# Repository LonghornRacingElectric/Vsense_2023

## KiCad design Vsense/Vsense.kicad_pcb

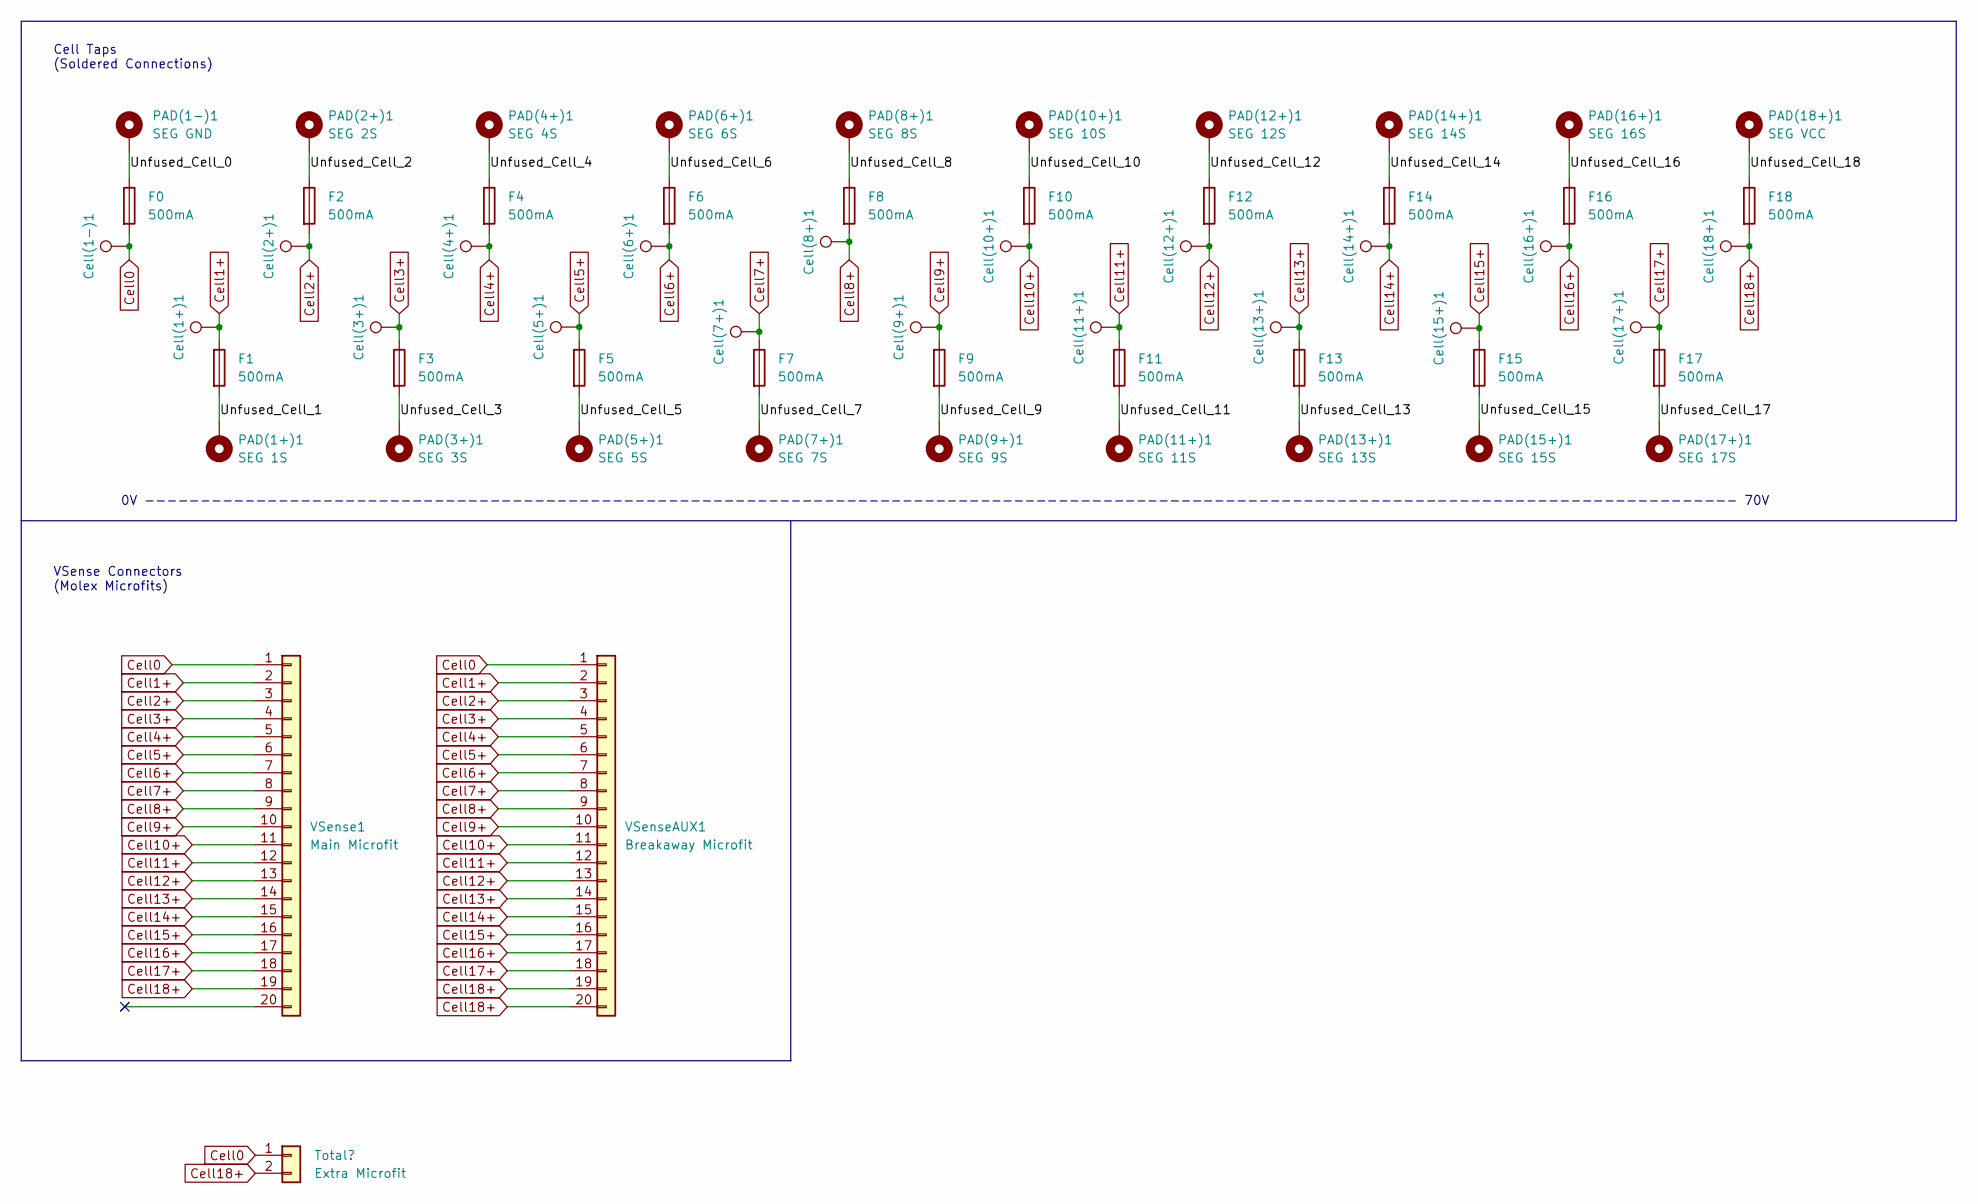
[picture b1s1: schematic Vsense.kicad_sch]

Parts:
Cell(1+)1, Cell(1-)1, Cell(2+)1, Cell(3+)1, Cell(4+)1, Cell(5+)1, Cell(6+)1, Cell(7+)1, Cell(8+)1, Cell(9+)1, Cell(10+)1, Cell(11+)1, Cell(12+)1, Cell(13+)1, Cell(14+)1, Cell(15+)1, Cell(16+)1, Cell(17+)1, Cell(18+)1: TestPoint; TestPoint_THTPad_2.0x2.0mm_Drill1.0mm
F0, F1, F2, F3, F4, F5, F6, F7, F8, F9, F10, F11, F12, F13, F14, F15, F16, F17, F18: 500mA; Fuse_1206_3216Metric_Pad1.42x1.75mm_HandSolder
PAD(1+)1: SEG 1S; TestPoint_Pad_4.0x4.0mm
PAD(1-)1: SEG GND; TestPoint_Pad_4.0x4.0mm
PAD(2+)1: SEG 2S; TestPoint_Pad_4.0x4.0mm
PAD(3+)1: SEG 3S; TestPoint_Pad_4.0x4.0mm
PAD(4+)1: SEG 4S; TestPoint_Pad_4.0x4.0mm
PAD(5+)1: SEG 5S; TestPoint_Pad_4.0x4.0mm
PAD(6+)1: SEG 6S; TestPoint_Pad_4.0x4.0mm
PAD(7+)1: SEG 7S; TestPoint_Pad_4.0x4.0mm
PAD(8+)1: SEG 8S; TestPoint_Pad_4.0x4.0mm
PAD(9+)1: SEG 9S; TestPoint_Pad_4.0x4.0mm
PAD(10+)1: SEG 10S; TestPoint_Pad_4.0x4.0mm
PAD(11+)1: SEG 11S; TestPoint_Pad_4.0x4.0mm
PAD(12+)1: SEG 12S; TestPoint_Pad_4.0x4.0mm
PAD(13+)1: SEG 13S; TestPoint_Pad_4.0x4.0mm
PAD(14+)1: SEG 14S; TestPoint_Pad_4.0x4.0mm
PAD(15+)1: SEG 15S; TestPoint_Pad_4.0x4.0mm
PAD(16+)1: SEG 16S; TestPoint_Pad_4.0x4.0mm
PAD(17+)1: SEG 17S; TestPoint_Pad_4.0x4.0mm
PAD(18+)1: SEG VCC; TestPoint_Pad_4.0x4.0mm
VSense1: Main Microfit; Molex_Micro-Fit_3.0_43045-2012_2x10_P3.00mm_Vertical
VSenseAUX1: Breakaway Microfit; Molex_Micro-Fit_3.0_43045-2021_2x10-1MP_P3.00mm_Horizontal

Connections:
/Unfused_Cell_0: F0.1, PAD(1-)1.1
/Unfused_Cell_1: F1.2, PAD(1+)1.1
/Unfused_Cell_2: F2.1, PAD(2+)1.1
/Unfused_Cell_3: F3.2, PAD(3+)1.1
/Unfused_Cell_4: F4.1, PAD(4+)1.1
/Unfused_Cell_5: F5.2, PAD(5+)1.1
/Unfused_Cell_6: F6.1, PAD(6+)1.1
/Unfused_Cell_7: F7.2, PAD(7+)1.1
/Unfused_Cell_8: F8.1, PAD(8+)1.1
/Unfused_Cell_9: F9.2, PAD(9+)1.1
/Unfused_Cell_10: F10.1, PAD(10+)1.1
/Unfused_Cell_11: F11.2, PAD(11+)1.1
/Unfused_Cell_12: F12.1, PAD(12+)1.1
/Unfused_Cell_13: F13.2, PAD(13+)1.1
/Unfused_Cell_14: F14.1, PAD(14+)1.1
/Unfused_Cell_15: F15.2, PAD(15+)1.1
/Unfused_Cell_16: F16.1, PAD(16+)1.1
/Unfused_Cell_17: F17.2, PAD(17+)1.1
/Unfused_Cell_18: F18.1, PAD(18+)1.1
Cell0: Cell(1-)1.1, F0.2, VSense1.1, VSenseAUX1.1; also elsewhere on the board
Cell1+: Cell(1+)1.1, F1.1, VSense1.2, VSenseAUX1.2
Cell2+: Cell(2+)1.1, F2.2, VSense1.3, VSenseAUX1.3
Cell3+: Cell(3+)1.1, F3.1, VSense1.4, VSenseAUX1.4
Cell4+: Cell(4+)1.1, F4.2, VSense1.5, VSenseAUX1.5
Cell5+: Cell(5+)1.1, F5.1, VSense1.6, VSenseAUX1.6
Cell6+: Cell(6+)1.1, F6.2, VSense1.7, VSenseAUX1.7
Cell7+: Cell(7+)1.1, F7.1, VSense1.8, VSenseAUX1.8
Cell8+: Cell(8+)1.1, F8.2, VSense1.9, VSenseAUX1.9
Cell9+: Cell(9+)1.1, F9.1, VSense1.10, VSenseAUX1.10
Cell10+: Cell(10+)1.1, F10.2, VSense1.11, VSenseAUX1.11
Cell11+: Cell(11+)1.1, F11.1, VSense1.12, VSenseAUX1.12
Cell12+: Cell(12+)1.1, F12.2, VSense1.13, VSenseAUX1.13
Cell13+: Cell(13+)1.1, F13.1, VSense1.14, VSenseAUX1.14
Cell14+: Cell(14+)1.1, F14.2, VSense1.15, VSenseAUX1.15
Cell15+: Cell(15+)1.1, F15.1, VSense1.16, VSenseAUX1.16
Cell16+: Cell(16+)1.1, F16.2, VSense1.17, VSenseAUX1.17
Cell17+: Cell(17+)1.1, F17.1, VSense1.18, VSenseAUX1.18
Cell18+: Cell(18+)1.1, F18.2, VSense1.19, VSenseAUX1.19, VSenseAUX1.20; also elsewhere on the board

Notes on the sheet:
0V ----------------------------------------------------------------------------------------------------------------------------------------------- 70V
Cell Taps (Soldered Connections)
VSense Connectors (Molex Microfits)

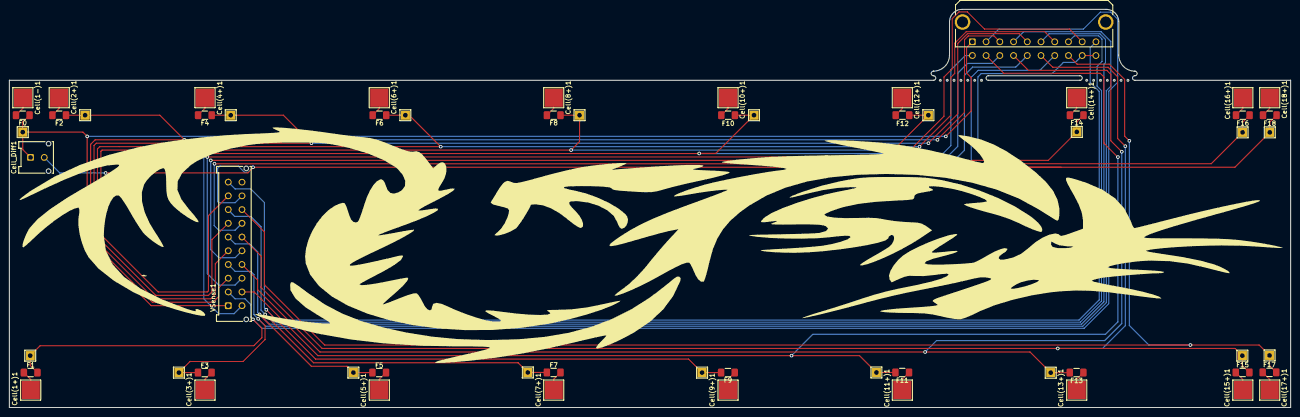
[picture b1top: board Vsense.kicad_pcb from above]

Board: 2 copper layers, 280.0 x 87.0 mm, 60 parts (0 on the bottom side), 38 nets.

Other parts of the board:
Cell_Diff1: Extra Microfit; Molex_Micro-Fit_3.0_43045-0212_2x01_P3.00mm_Vertical

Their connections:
Cell0: Cell_Diff1.1; also elsewhere on the board
Cell18+: Cell_Diff1.2; also elsewhere on the board

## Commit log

2023-02-26 Added Gerbers
